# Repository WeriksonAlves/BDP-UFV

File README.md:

# Werikson_BDP
BDP - Equipe de Futebol de Robôs da UFV.

Códigos referentes a plataforma de gerenciamento de partidas. Realiza o processamenot de imagem, comunicação e controle do robôs.

PLATAFORMA NÃO OTIMIZADA

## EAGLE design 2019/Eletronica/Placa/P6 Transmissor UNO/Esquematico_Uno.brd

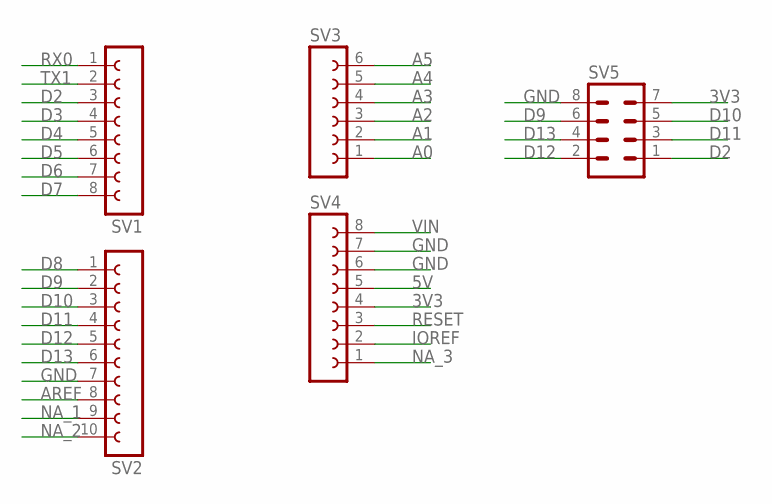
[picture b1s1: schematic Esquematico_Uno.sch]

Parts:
SV1, SV4: FE08-1; FE08
SV2: FE10-1; FE10
SV3: FE06-1; FE06
SV5: MA04-2

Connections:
3V3: SV4.4, SV5.7
5V: SV4.5
A0: SV3.1
A1: SV3.2
A2: SV3.3
A3: SV3.4
A4: SV3.5
A5: SV3.6
AREF: SV2.8
D2: SV1.3, SV5.1
D3: SV1.4
D4: SV1.5
D5: SV1.6
D6: SV1.7
D7: SV1.8
D8: SV2.1
D9: SV2.2, SV5.6
D10: SV2.3, SV5.5
D11: SV2.4, SV5.3
D12: SV2.5, SV5.2
D13: SV2.6, SV5.4
GND: SV2.7, SV4.6, SV4.7, SV5.8
IOREF: SV4.2
NA_1: SV2.9
NA_2: SV2.10
NA_3: SV4.1
RESET: SV4.3
RX0: SV1.1
TX1: SV1.2
VIN: SV4.8

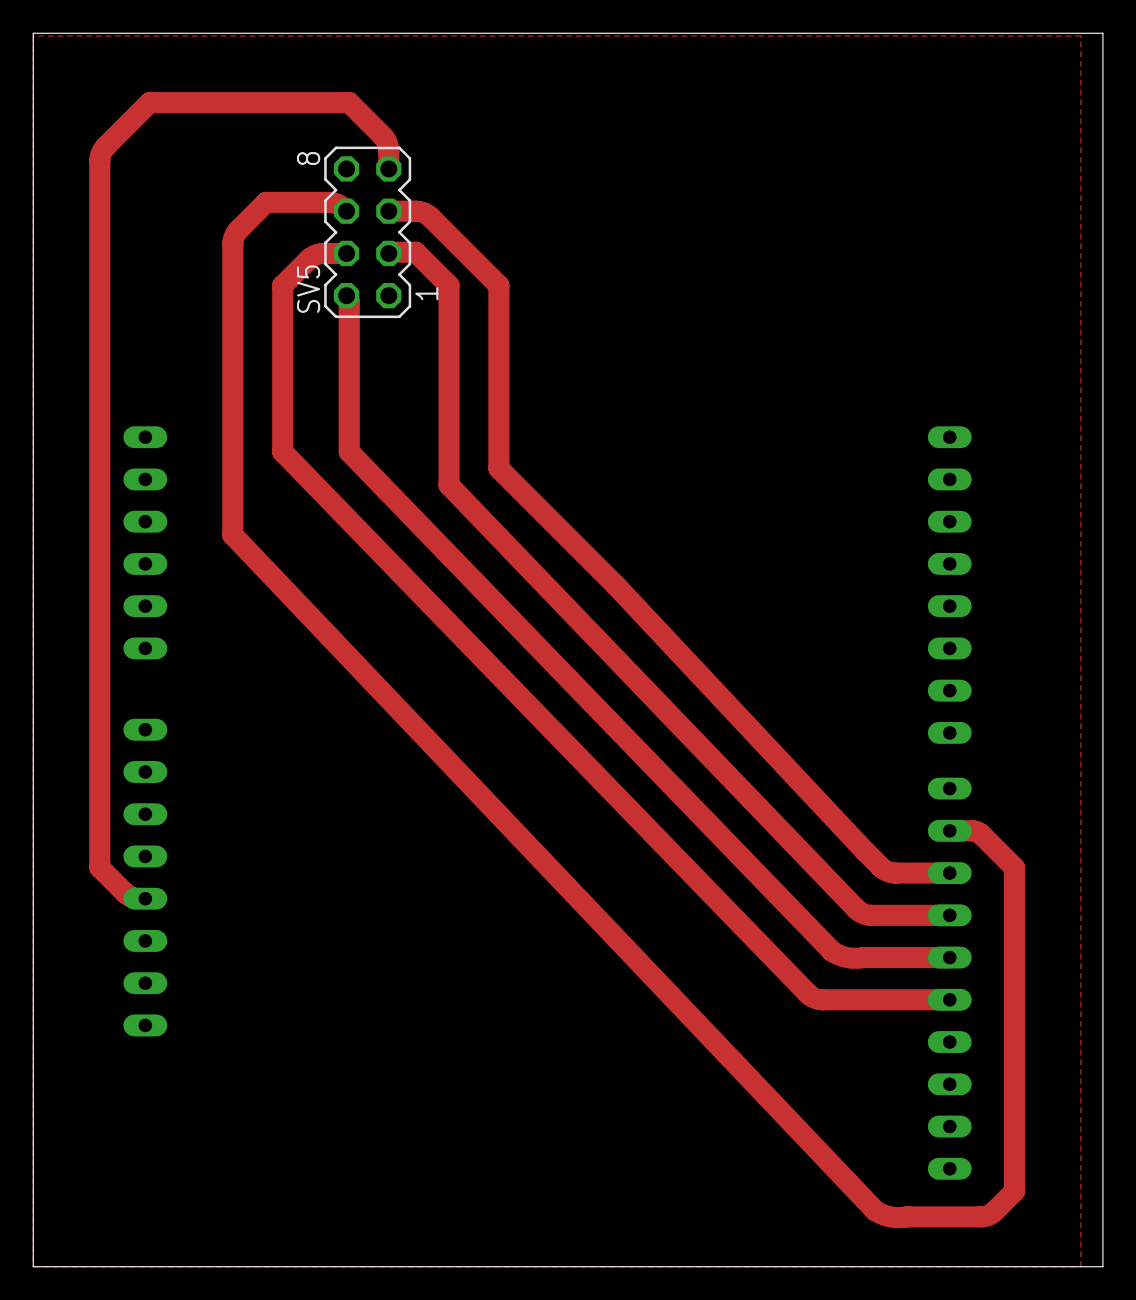
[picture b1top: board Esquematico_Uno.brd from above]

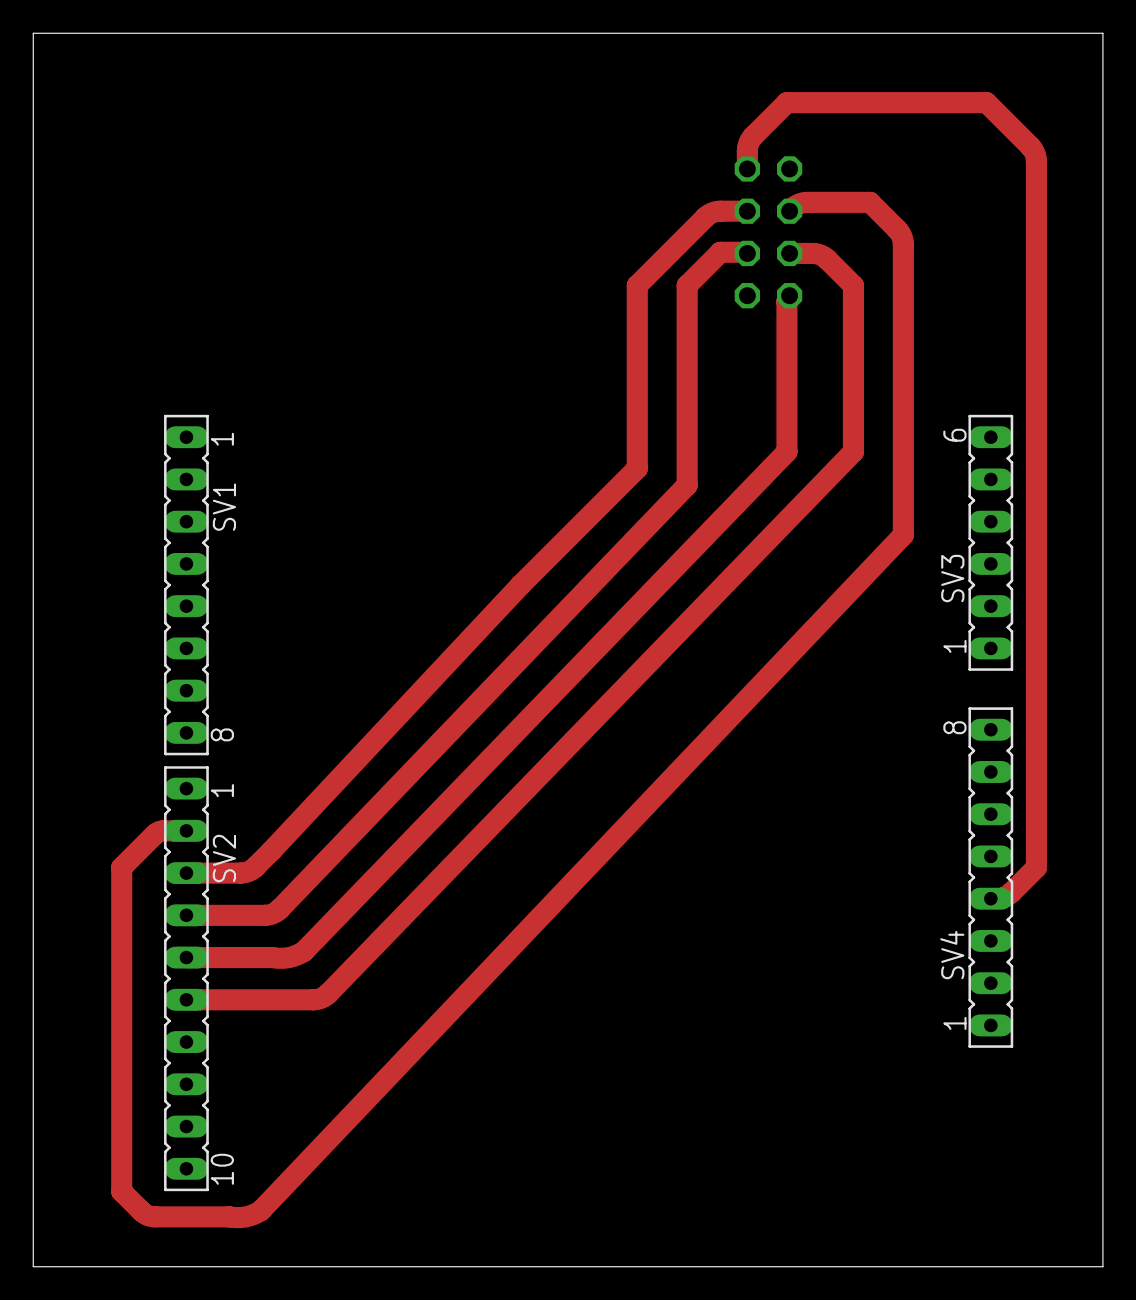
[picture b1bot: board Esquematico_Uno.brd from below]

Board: 2 copper layers, 64.3 x 74.2 mm, 5 parts (4 on the bottom side), 8 nets.

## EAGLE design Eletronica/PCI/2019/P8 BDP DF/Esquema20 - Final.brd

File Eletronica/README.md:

# BDP_Eletronica
Repositório relacionada a eletrônica.

Na pasta Arduino se encontra a programação feita para ser usada no microcontrolador dos robôs,
sendo o "sender10" a programação PC <-> Robô e a "receiver10" a Sender <-> Robô.

Na pasta PCI se encontra o projeto da placa eletrônica dos robôs.

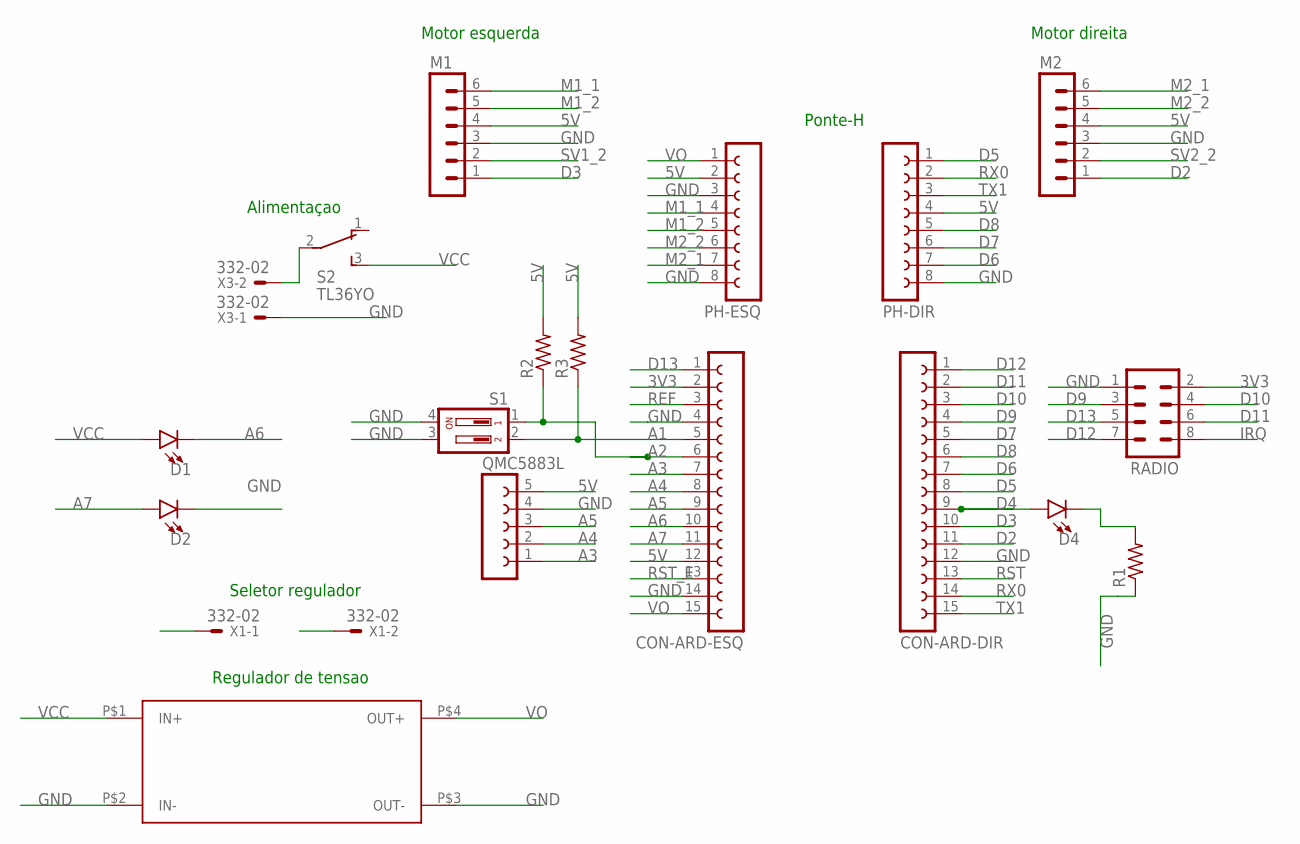
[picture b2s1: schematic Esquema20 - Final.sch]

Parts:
CON-ARD-DIR: FE15-1; FE15
CON-ARD-ESQ: FE15-1; FE15
D1, D2, D4: LED-3MM-NO_SILK; LED_3MM-NS
M1, M2: MA06-1
PH-DIR: FE08-1; FE08
PH-ESQ: FE08-1; FE08
QMC5883L: FE05W
R1, R2, R3: R-US_0207/12; 0207/12
RADIO: MA04-2
S1: DA02; DA-02
S2: TL36YO; TL3XYO
U$1: REGULADOR; REGULADOR-FP
X1, X3: 332-02

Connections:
3V3: CON-ARD-ESQ.2, RADIO.2
5V: CON-ARD-ESQ.12, M1.4, M2.4, PH-DIR.4, PH-ESQ.2, QMC5883L.5, R2.2, R3.2
A1: CON-ARD-ESQ.5, R3.1, S1.2
A2: CON-ARD-ESQ.6, R2.1, S1.1
A3: CON-ARD-ESQ.7, QMC5883L.1
A4: CON-ARD-ESQ.8, QMC5883L.2
A5: CON-ARD-ESQ.9, QMC5883L.3
A6: CON-ARD-ESQ.10, D1.K (C)
A7: CON-ARD-ESQ.11, D2.A
D2: CON-ARD-DIR.11, M2.1
D3: CON-ARD-DIR.10, M1.1
D4: CON-ARD-DIR.9, D4.A
D5: CON-ARD-DIR.8, PH-DIR.1
D6: CON-ARD-DIR.7, PH-DIR.7
D7: CON-ARD-DIR.5, PH-DIR.6
D8: CON-ARD-DIR.6, PH-DIR.5
D9: CON-ARD-DIR.4, RADIO.3
D10: CON-ARD-DIR.3, RADIO.4
D11: CON-ARD-DIR.2, RADIO.6
D12: CON-ARD-DIR.1, RADIO.7
D13: CON-ARD-ESQ.1, RADIO.5
GND: CON-ARD-DIR.12, CON-ARD-ESQ.4, CON-ARD-ESQ.14, D2.K (C), M1.3, M2.3, PH-DIR.8, PH-ESQ.3, PH-ESQ.8, QMC5883L.4, R1.1, RADIO.1, S1.3, S1.4, U$1.P$2 (IN-), U$1.P$3 (OUT-), X3.1
IRQ: RADIO.8
M1_1: M1.6, PH-ESQ.4
M1_2: M1.5, PH-ESQ.5
M2_1: M2.6, PH-ESQ.7
M2_2: M2.5, PH-ESQ.6
unnamed: S2.2, X3.2
unnamed: D4.K (C), R1.2
REF: CON-ARD-ESQ.3
RST: CON-ARD-DIR.13
RST_E: CON-ARD-ESQ.13
RX0: CON-ARD-DIR.14, PH-DIR.2
SV1_2: M1.2
SV2_2: M2.2
TX1: CON-ARD-DIR.15, PH-DIR.3
VCC: D1.A, S2.3 (S), U$1.P$1 (IN+), X1.1
VO: CON-ARD-ESQ.15, PH-ESQ.1, U$1.P$4 (OUT+), X1.2

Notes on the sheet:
Motor direita
Motor esquerda
Alimentaçao
Ponte-H
Regulador de tensao
Seletor regulador

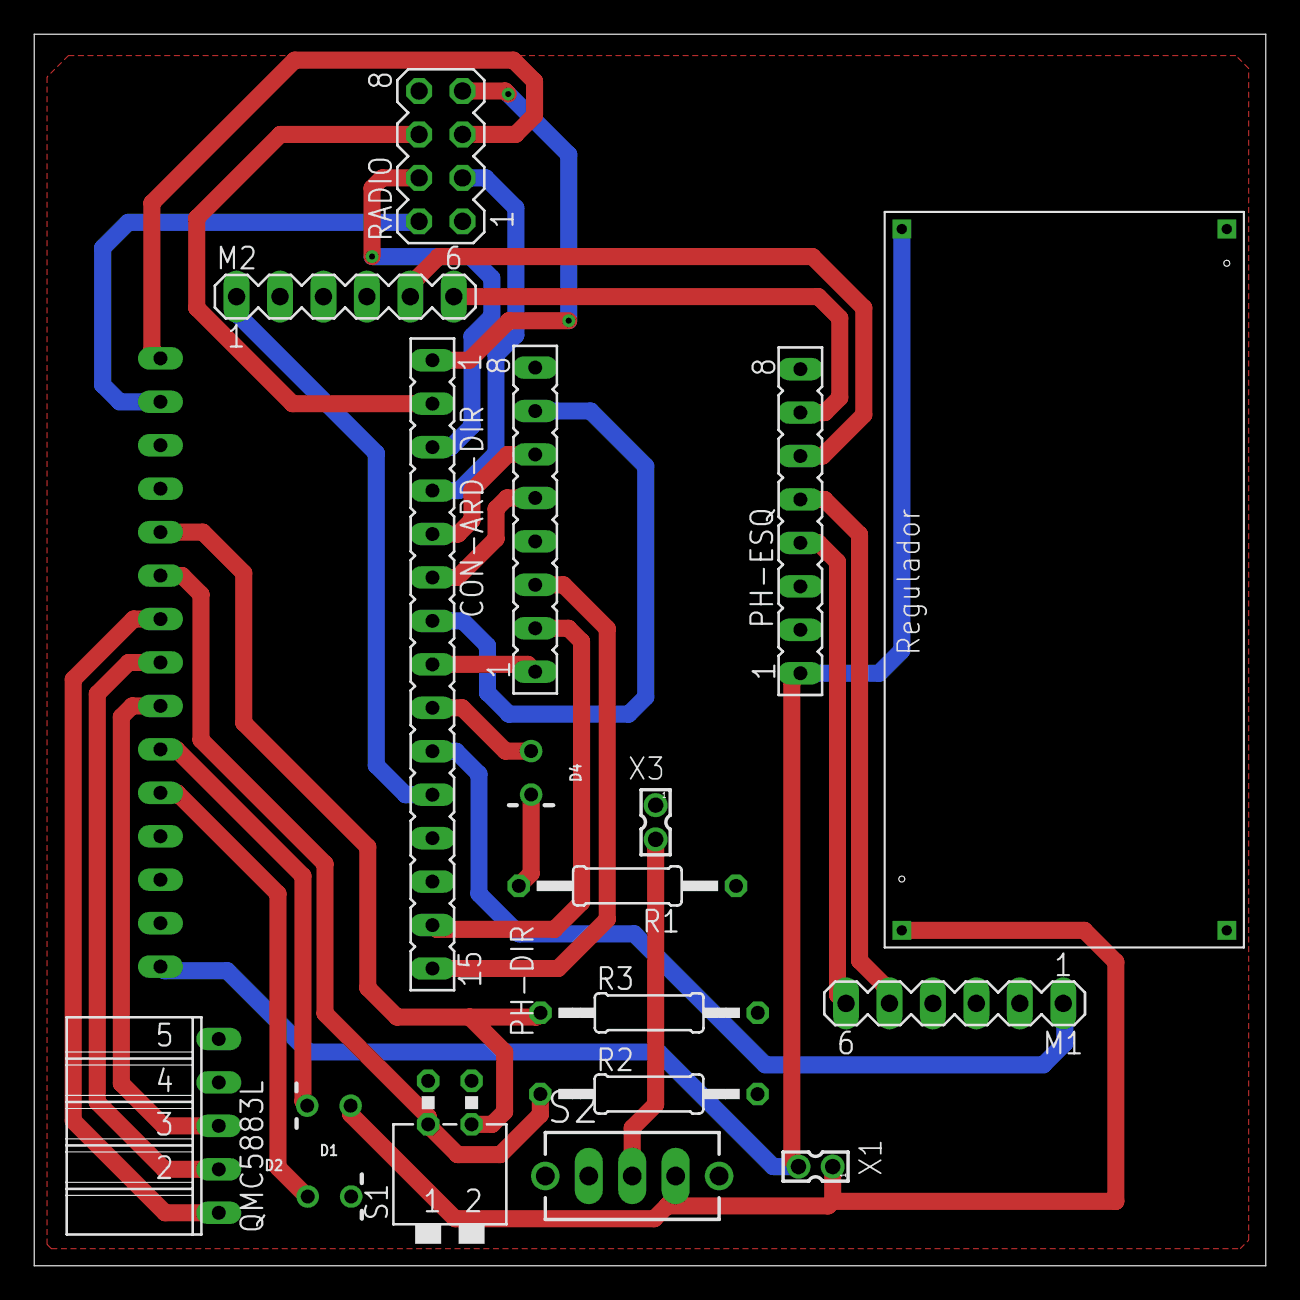
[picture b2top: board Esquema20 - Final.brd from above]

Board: 2 copper layers, 72.0 x 72.0 mm, 19 parts (1 on the bottom side), 32 nets.

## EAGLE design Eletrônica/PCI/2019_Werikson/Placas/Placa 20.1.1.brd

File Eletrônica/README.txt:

Na pasta Arduino se encontra a programação feita para ser usada no microcontrolador dos robôs,
sendo o "sender10" a programação PC <-> Robô e a "receiver10" a Sender <-> Robô.

Na pasta EAGLE se encontra o projeto da placa eletrônica dos robôs.

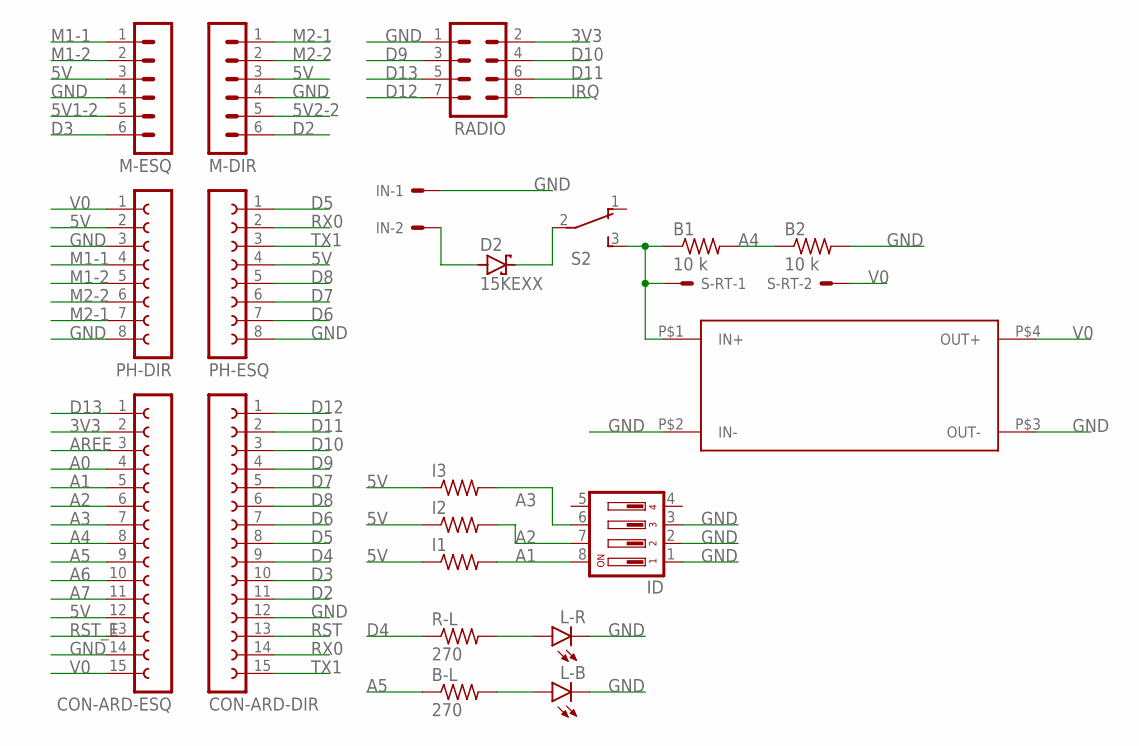
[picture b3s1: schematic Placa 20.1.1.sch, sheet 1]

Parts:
B1, B2: 10 k; 0207/10
B-L: 270; 0207/10
CON-ARD-DIR: FE15-1; FE15
CON-ARD-ESQ: FE15-1; FE15
D2: 15KEXX; CB429-17
I1, I2, I3: R-US_0207/10; 0207/10
ID: DA04; DA-04
IN: 332-02
L-B: LED5MM
L-R: LED5MM
M-DIR: MA06-1
M-ESQ: MA06-1
PH-DIR: FE08-1; FE08
PH-ESQ: FE08-1; FE08
R-L: 270; 0207/10
RADIO: MA04-2
REGULADOR-DE-TENSÃO: REGULADOR; REGULADOR-FP
S2: TL36YO; TL3XYO
S-RT: 332-02

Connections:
3V3: CON-ARD-ESQ.2, RADIO.2
5V: CON-ARD-ESQ.12, I1.1, I2.1, I3.1, M-DIR.3, M-ESQ.3, PH-DIR.2, PH-ESQ.4
5V1-2: M-ESQ.5
5V2-2: M-DIR.5
A0: CON-ARD-ESQ.4
A1: CON-ARD-ESQ.5, I1.2, ID.8
A2: CON-ARD-ESQ.6, I2.2, ID.7
A3: CON-ARD-ESQ.7, I3.2, ID.6
A4: B1.2, B2.1, CON-ARD-ESQ.8
A5: B-L.1, CON-ARD-ESQ.9
A6: CON-ARD-ESQ.10
A7: CON-ARD-ESQ.11
AREE: CON-ARD-ESQ.3
D2: CON-ARD-DIR.11, M-DIR.6
D3: CON-ARD-DIR.10, M-ESQ.6
D4: CON-ARD-DIR.9, R-L.1
D5: CON-ARD-DIR.8, PH-ESQ.1
D6: CON-ARD-DIR.7, PH-ESQ.7
D7: CON-ARD-DIR.5, PH-ESQ.6
D8: CON-ARD-DIR.6, PH-ESQ.5
D9: CON-ARD-DIR.4, RADIO.3
D10: CON-ARD-DIR.3, RADIO.4
D11: CON-ARD-DIR.2, RADIO.6
D12: CON-ARD-DIR.1, RADIO.7
D13: CON-ARD-ESQ.1, RADIO.5
GND: B2.2, CON-ARD-DIR.12, CON-ARD-ESQ.14, ID.1, ID.2, ID.3, IN.1, L-B.K (C), L-R.K (C), M-DIR.4, M-ESQ.4, PH-DIR.3, PH-DIR.8, PH-ESQ.8, RADIO.1, REGULADOR-DE-TENSÃO.P$2 (IN-), REGULADOR-DE-TENSÃO.P$3 (OUT-)
IRQ: RADIO.8
M1-1: M-ESQ.1, PH-DIR.4
M1-2: M-ESQ.2, PH-DIR.5
M2-1: M-DIR.1, PH-DIR.7
M2-2: M-DIR.2, PH-DIR.6
unnamed: D2.A, IN.2
unnamed: D2.C, S2.2
unnamed: B1.1, REGULADOR-DE-TENSÃO.P$1 (IN+), S2.3 (S), S-RT.1
unnamed: L-R.A, R-L.2
unnamed: B-L.2, L-B.A
RST: CON-ARD-DIR.13
RST_E: CON-ARD-ESQ.13
RX0: CON-ARD-DIR.14, PH-ESQ.2
TX1: CON-ARD-DIR.15, PH-ESQ.3
V0: CON-ARD-ESQ.15, PH-DIR.1, REGULADOR-DE-TENSÃO.P$4 (OUT+), S-RT.2

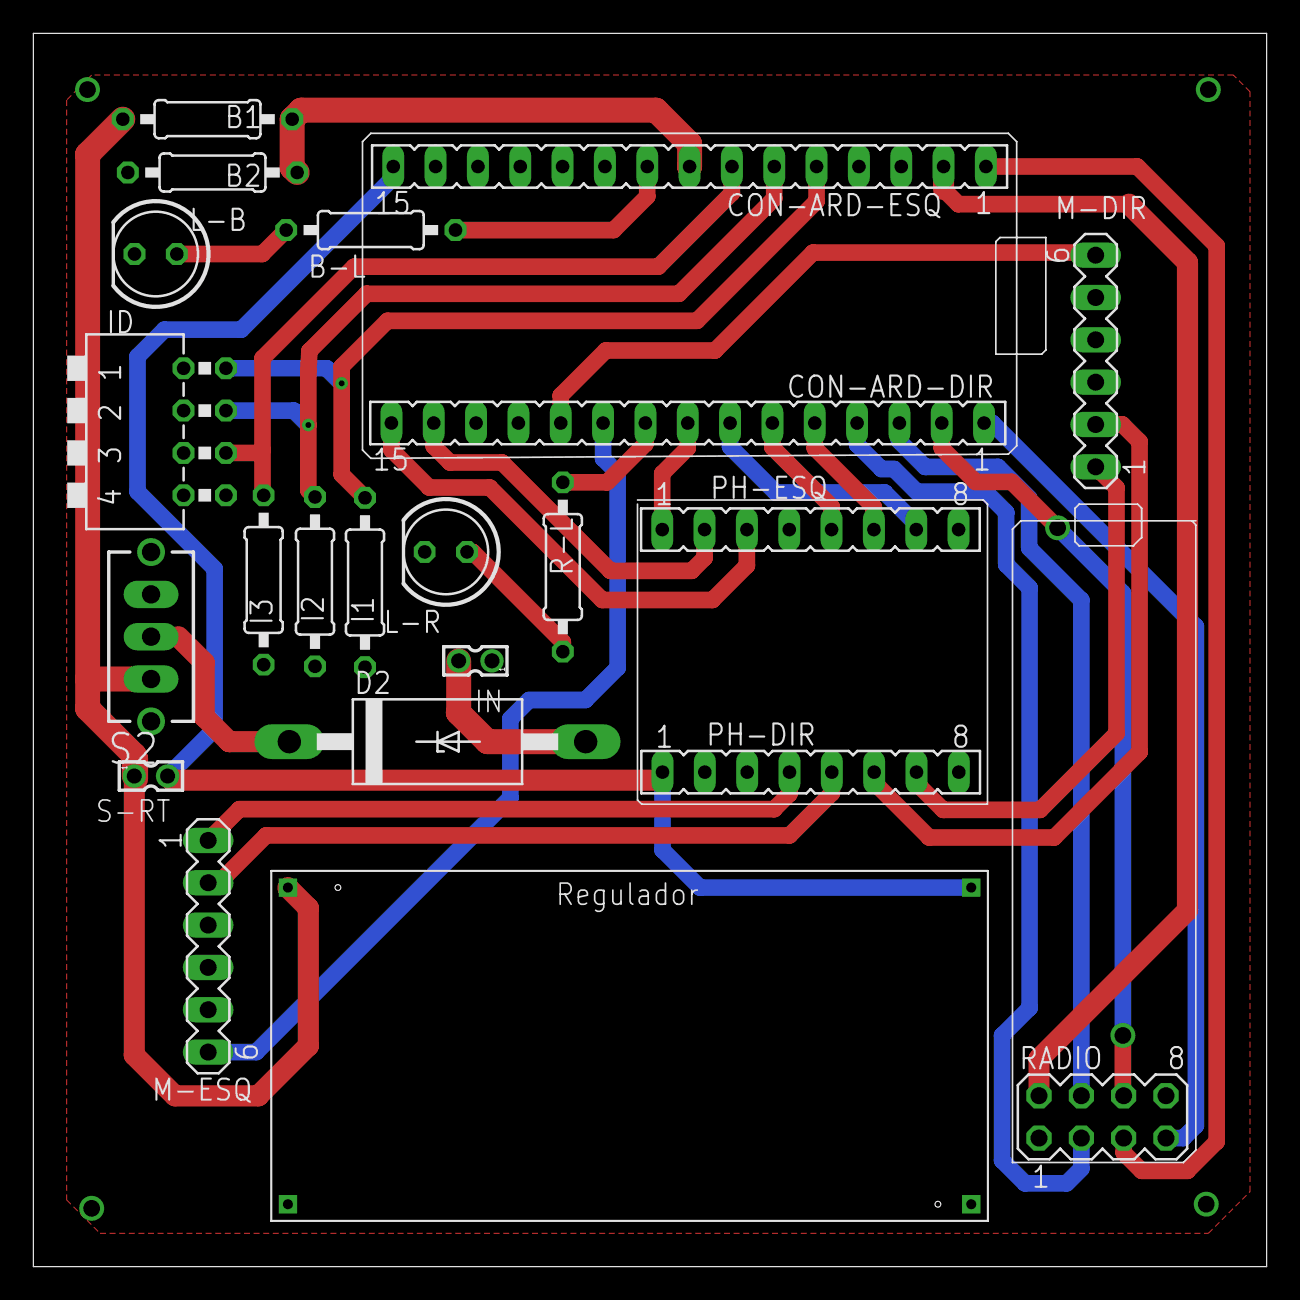
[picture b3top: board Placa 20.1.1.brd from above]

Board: 2 copper layers, 74.0 x 74.0 mm, 22 parts (0 on the bottom side), 32 nets.

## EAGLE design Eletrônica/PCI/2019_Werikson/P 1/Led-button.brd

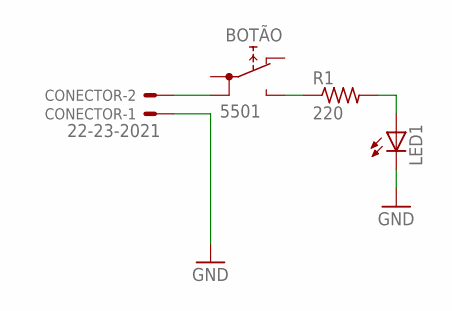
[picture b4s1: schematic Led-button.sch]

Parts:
BOTÃO: 5501
CONECTOR: 22-23-2021
LED1: LED5MM
R1: 220; 0204/7

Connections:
GND: CONECTOR.1, LED1.K (C)
unnamed: BOTÃO.1B, CONECTOR.2
unnamed: LED1.A, R1.2
unnamed: BOTÃO.NO, R1.1

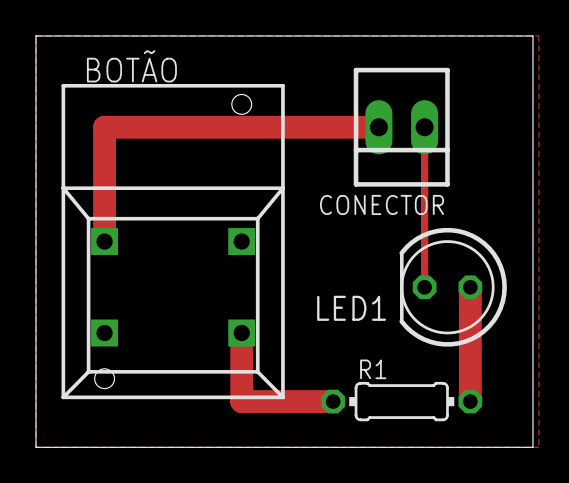
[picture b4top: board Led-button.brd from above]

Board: 2 copper layers, 27.6 x 22.8 mm, 4 parts (0 on the bottom side), 4 nets.

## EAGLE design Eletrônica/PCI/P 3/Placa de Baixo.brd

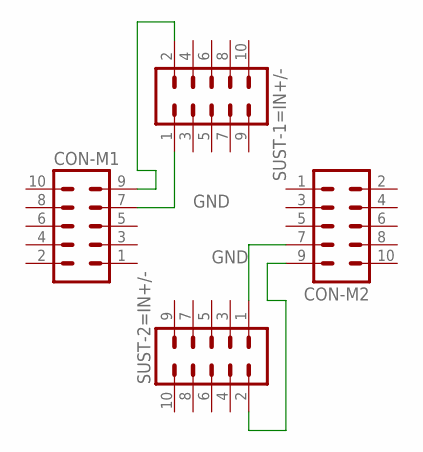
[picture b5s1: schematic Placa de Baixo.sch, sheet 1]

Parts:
CON-M1, CON-M2: ML10-3ML; 3M_10L
SUST-1=IN+/-, SUST-2=IN+/-: MA05-2

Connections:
GND: CON-M1.7, CON-M2.7, SUST-1=IN+/-.1, SUST-2=IN+/-.1
unnamed: CON-M1.9, SUST-1=IN+/-.2
unnamed: CON-M2.9, SUST-2=IN+/-.2

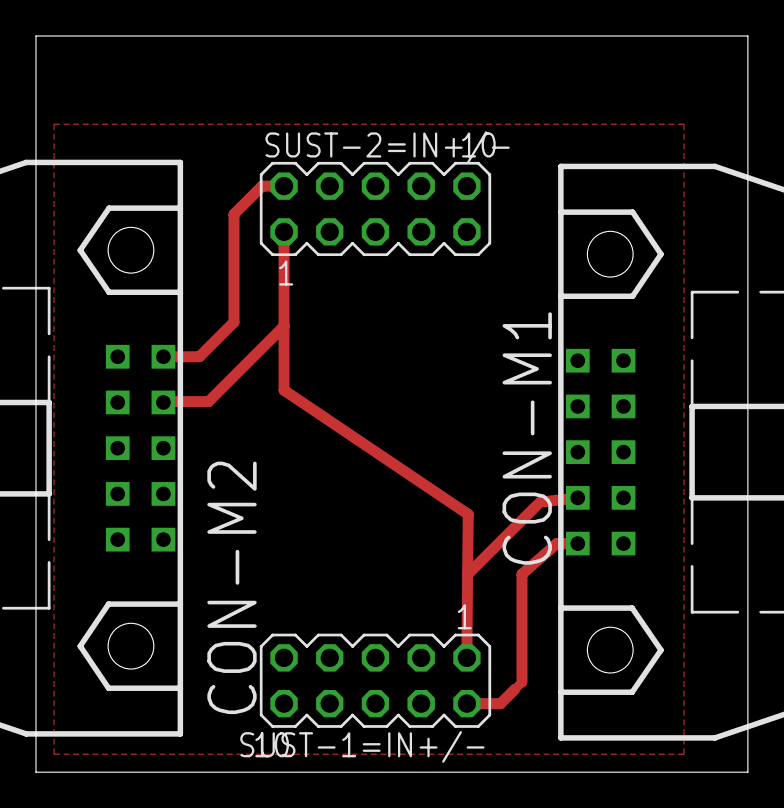
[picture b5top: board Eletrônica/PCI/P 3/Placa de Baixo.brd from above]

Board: 2 copper layers, 39.5 x 40.9 mm, 4 parts (0 on the bottom side), 3 nets.

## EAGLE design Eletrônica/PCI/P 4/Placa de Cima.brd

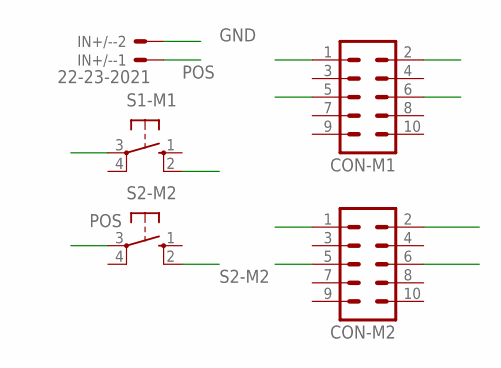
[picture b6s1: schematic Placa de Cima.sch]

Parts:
CON-M1, CON-M2: MA05-2
IN+/-: 22-23-2021
S1-M1, S2-M2: 10-XX; B3F-10XX

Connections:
GND: CON-M1.5, CON-M1.6, CON-M2.5, CON-M2.6, IN+/-.2
POS: IN+/-.1, S1-M1.3, S2-M2.3
S1-M1: CON-M1.1, CON-M1.2, S1-M1.2 (S1)
S2-M2: CON-M2.1, CON-M2.2, S2-M2.2 (S1)

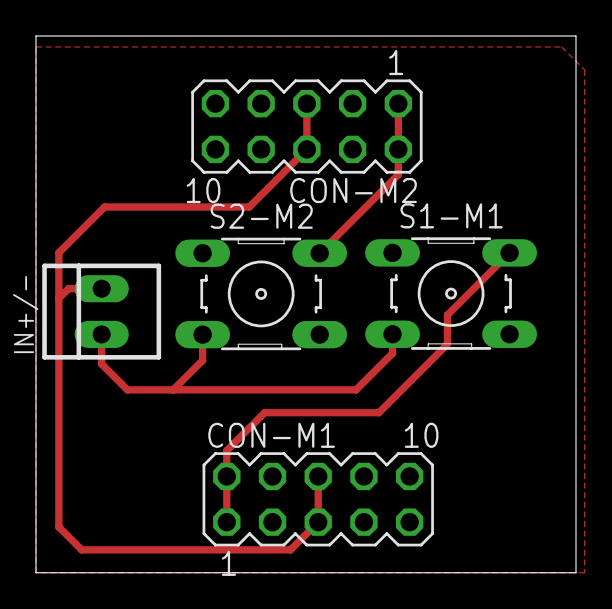
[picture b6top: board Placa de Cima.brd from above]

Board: 2 copper layers, 30.0 x 29.8 mm, 5 parts (0 on the bottom side), 4 nets.

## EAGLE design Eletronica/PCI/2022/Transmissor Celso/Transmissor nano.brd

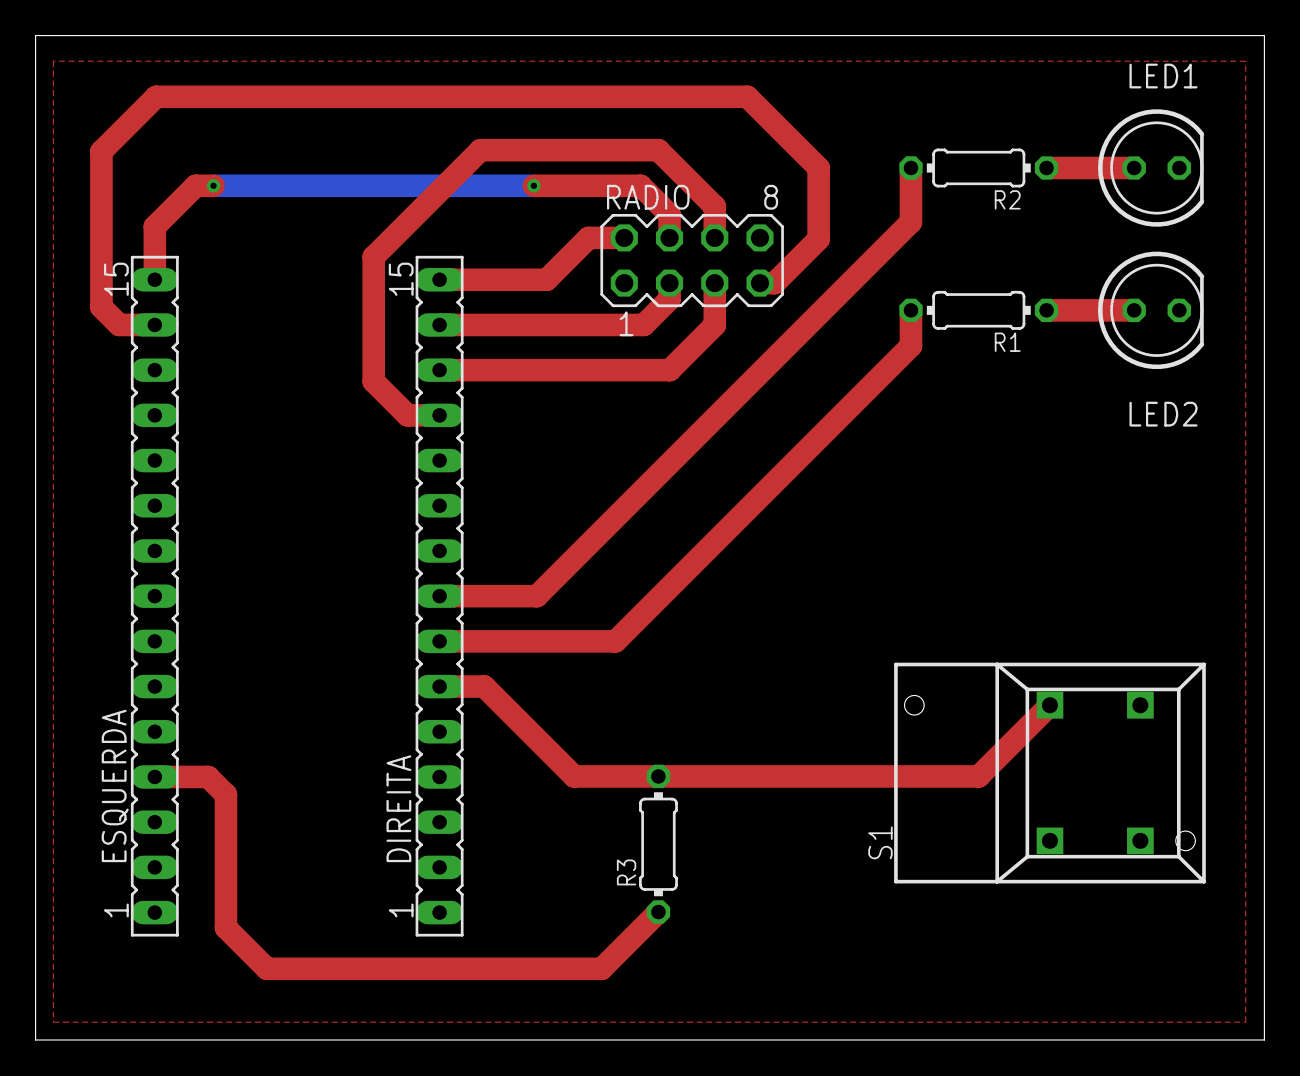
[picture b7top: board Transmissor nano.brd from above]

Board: 2 copper layers, 69.0 x 56.4 mm, 9 parts (0 on the bottom side), 13 nets.

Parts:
DIREITA: FE15
ESQUERDA: FE15
LED1, LED2: LED5MM
R1, R2, R3: 0204/7
RADIO: MA04-2
S1: 5501

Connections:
3V3: ESQUERDA.14, RADIO.7
5V: ESQUERDA.4, R3.1
D3: DIREITA.6, R3.2, S1.1A
D4: DIREITA.7, R1.2
D5: DIREITA.8, R2.2
D9: DIREITA.12, RADIO.6
D10: DIREITA.13, RADIO.5
D11: DIREITA.14, RADIO.3
D12: DIREITA.15, RADIO.2
D13: ESQUERDA.15, RADIO.4
GND: DIREITA.4, ESQUERDA.2, LED1.K, LED2.K, RADIO.8, S1.NC
unnamed: LED1.A, R2.1
unnamed: LED2.A, R1.1

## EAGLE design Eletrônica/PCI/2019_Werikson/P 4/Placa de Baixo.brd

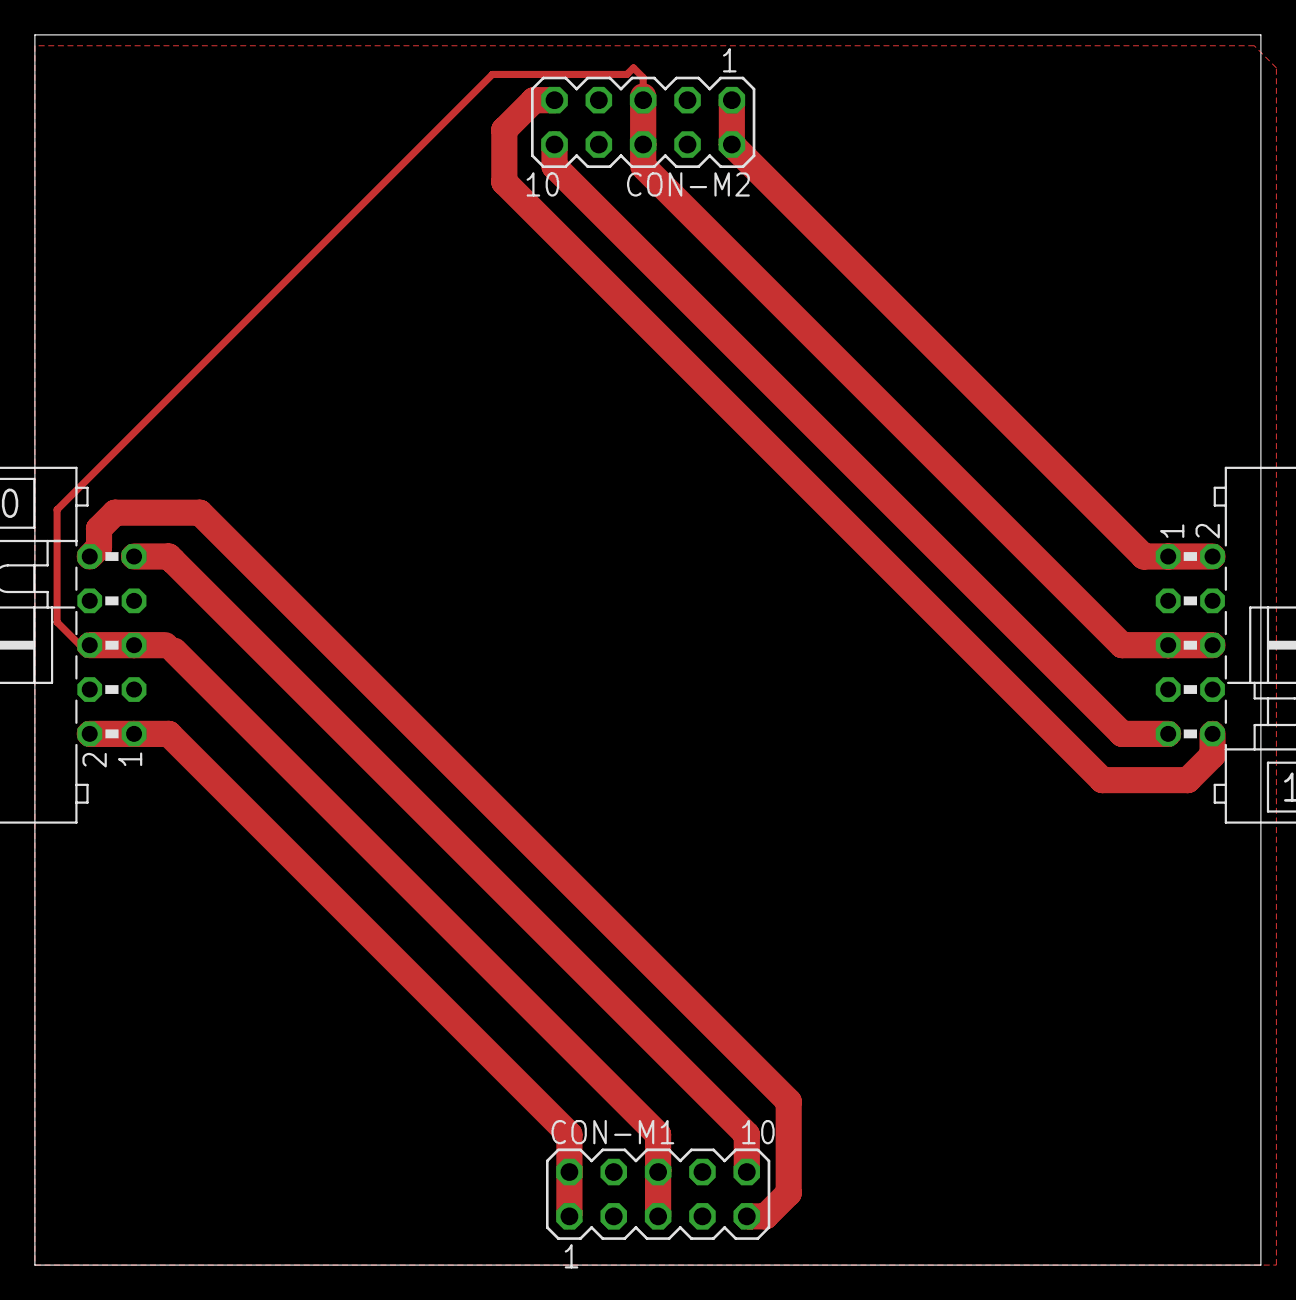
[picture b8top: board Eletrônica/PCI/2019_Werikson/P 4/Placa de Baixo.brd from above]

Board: 2 copper layers, 70.2 x 70.5 mm, 4 parts (0 on the bottom side), 7 nets.

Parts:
CON-M1, CON-M2: MA05-2
ENCAIXE1, ENCAIXE2: ML10L

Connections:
COMANDO-1: CON-M1.9, ENCAIXE1.10
COMANDO-2: CON-M1.10, ENCAIXE1.9
COMANDO-A: CON-M2.9, ENCAIXE2.10
COMANDO-B: CON-M2.10, ENCAIXE2.9
GND: CON-M1.5, CON-M1.6, CON-M2.5, CON-M2.6, ENCAIXE1.5, ENCAIXE1.6, ENCAIXE2.5, ENCAIXE2.6
S1-M1: CON-M1.1, CON-M1.2, ENCAIXE1.1, ENCAIXE1.2
S2-M2: CON-M2.1, CON-M2.2, ENCAIXE2.1, ENCAIXE2.2

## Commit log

2022-04-22 Organizando
    Organizando os arquivos para a competição de 2022
2022-04-22 Organizando
2022-04-23 quase
2022-04-23 Atualizado 22/04
    Arquivos atualizados em suas respectivas pastas.
2022-04-28 Transmissor 22.1
    Foi feito os comentários no código e ajustado alguns detalhes no código.
2022-04-28 Transmissor 22.1
2022-04-28 Atualizando o receptor
2022-05-03 Atualizando
2022-05-04 up cam
2022-05-04 Menu camera
2022-05-04 Testando branch
2022-05-04 OK?
    Deu um problema aqui com as branchs, mas acho que consegui arrumar, verifica se os arquivos estão todos certo primeiro.
2022-05-04 04/05
2022-05-10 teste comit e push
2022-05-10 testebranch
2022-05-10 remove "bool ok" and add while
    while é para garantir que o pacote será escrito.
2022-05-11 save
2022-05-11 complete
2022-05-11 Menu camera
    Concluida a criação do menu da camera.
2022-05-13 Nome
    Alterei os nome de alguns arquivos.
2022-05-13 Contimnuação
2022-05-31 atualização nova piangem
2022-06-01 Não existe mais
2022-06-29 Projeto BDP 2023
2022-08-06 Revisão do código transmissor
    O código atual está com os pinos antigos, canal 82 de comunicação, seção para verificar a taxa de perdas, led para envio de dados e rotina de teste de comunicação.
2022-08-16 Receptor semi ok
2022-08-17 Codigo Revisado: Sender e Receiver OK
2022-08-18 Org2
2022-09-29 Atualização para a competição LARS 2022
2023-01-31 Plataforma OK
2023-02-01 Atualizando sistema principal
    Conversão matlab para python finalizada.
    Adicionando a eletrônica 2023
2023-02-06 Atualização de arquivos de anos anteriores
2023-03-24 Atualização dos arquivos do pc do nero
2023-03-26 Acrescentado a função para joystick
2023-03-26 Controle e joystick completos
2023-03-30 atualizando pygame
2023-05-02 Câmera, Cor e Campo estão ok
2023-05-02 Talvez esta pronto
2023-07-13 Organização do Git BDP
    DE 2018 ate 2022 está Ok. Só passar para o Git oficial.
2023-08-06 Versão corrigida
2023-08-26 Inicio da implementação de 3 tags e teste mecânico
2023-08-26 ok Início da correção de 3 tags e teste mecânico
2023-08-31 Posição com 3 Cores OK
    Falta a orientação
2023-09-01 Postura Completa OK
    Falta implementar os desenhos representando a segmentação.
2023-09-02 Correção da Postura completa
    Falta arrumar a visão de segmentação
2023-09-02 FAlta a visao segmentada
2023-09-02 Postura e angulo completo com 3 Cores
    Iniciando joystick
2023-09-03 Implementando o Juiz 2x
2023-09-03 MElhoria
    Falta melhorar o tempo
2023-09-03 Joystick implementado
2023-09-03 Fim do BDP Weekend
2023-09-22 Atualização para a nova versão da plataforma
    BDP Weekend
2023-09-22 Implementando a classe dos jogadores
    Foi baseada na classe do Pioneer do matlab, atualmente trabalhando na função de controle e nos ganhos.
2023-09-26 Implementação do controle de posição
    O controle pela simulação está funcionando, porem falta refinar a comunicação com o robô real e sincronizar as variáveis com a da plataforma.
2023-09-29 Implementação do controle (Hiago)
    O controle proposto, funciona e está bom para medias distâncias. É passível de melhorias no ganhos.
2023-10-02 Implementando o juiz
2023-10-03 Implementação do juiz
    Falta validar o posicionamento automático
2023-10-05 Resumo dia 03-10
2023-10-05 Implementação do atacante e goleiro
    Incompleto
2023-10-10 Código da vitoria
    Vencemos o BahiaRT
2023-10-10 Correção da resolução da camera
2023-10-12 Implementação da otimização
    Os métodos principais da calibração da câmera e da calibração das cores já foram passadas, falta corrigir alguns pequenos problemas.
2023-12-19 Última versão atualizada
    Projeto interrompido. A plataforma foi validada e está funcional, cabendo otimizações no código e busca por bugs.

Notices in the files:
parts and their libraries:
SparkFun-LED: Licensing: Creative Commons ShareAlike 4.0 International - https://creativecommons.org/licenses/by-sa/4.0
